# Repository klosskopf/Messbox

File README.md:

Dieses Repository beinhaltet alle Dateien zum Projekt Messbox 2000

Im Ordner *Raspberry* befindet sich der QT 5.11.3 C++ Code für die Middleware und Kennlinienerzeugung
Die Software muss mit root-Rechten ausgeführt werden. Damit die Aplikation ein Gui anzeigen kann,  
muss ```export XAUTHORITY=/home/pi/.Xauthority``` an /etc/profiles angehängt werden.

Im Ordner *Basisplatine* findet sich der Schaltplan und Layout für die Basisplatine

Im Ordner *STM32* befindet sich der C Code für die STM32 uC

Im Ordner *Steckkarte* befindet sich der Schaltplan und Layout für die Steckkarte.

Im Ordner *ATMEGA88* befindet sich der C Code für den atmega88 zur Erzeugung der sample frequenz und allgemeines

Im Ordner *BOM* finden sich Stücklisten und Bestellungsinfos für JLCPCB

Im Ordner *doc* finden sich alle Schemata, die das System beschreiben

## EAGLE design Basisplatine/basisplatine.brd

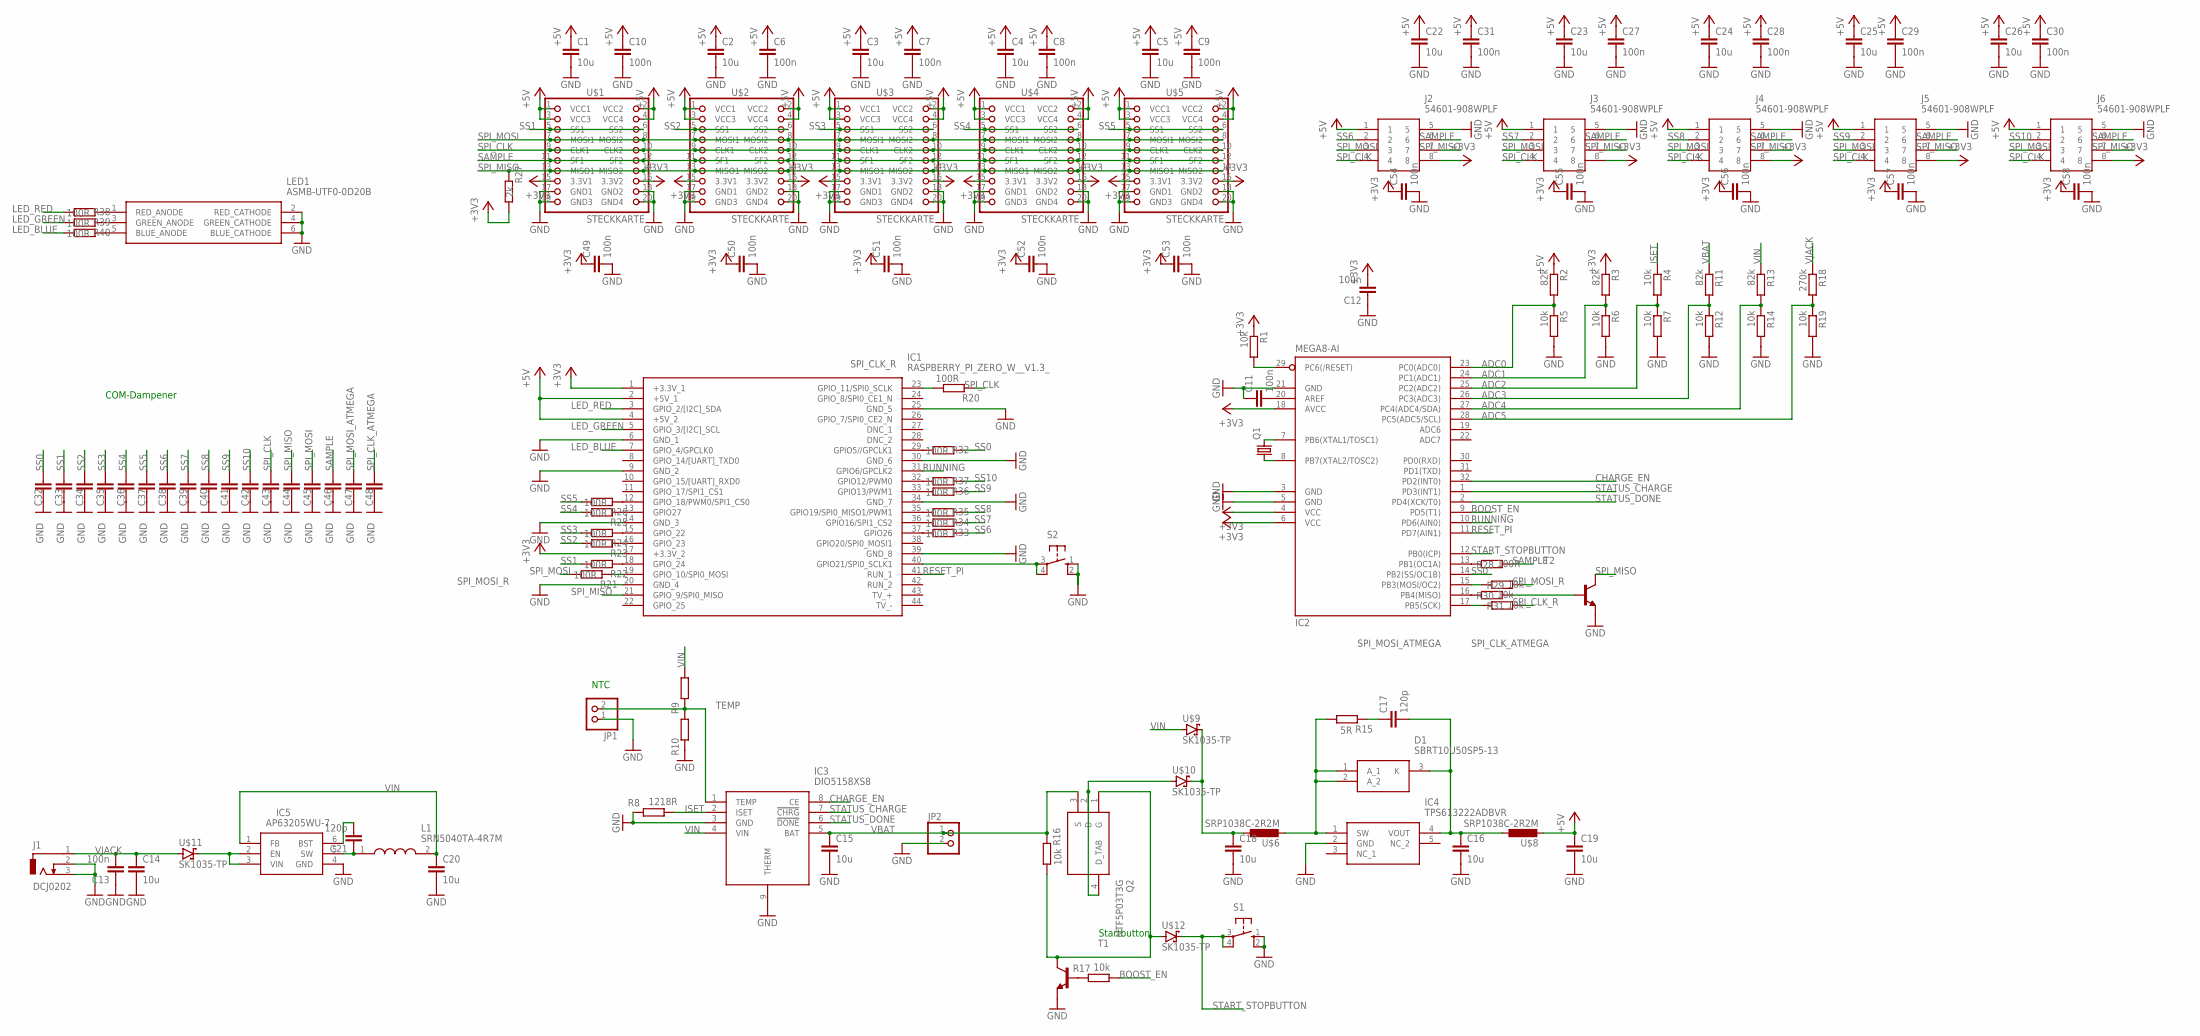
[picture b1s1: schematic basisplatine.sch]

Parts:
C1, C22: 10u; C1206
C2, C3, C4, C5, C14, C15, C16, C18, C19, C20, C23, C24, C25, C26: 10u; C1206K
C6, C7, C8, C9, C10, C11, C12, C13, C27, C28, C29, C30, C31, C49, C50, C51, C52, C53, C54, C55, C56, C57, C58: 100n; C0603K
C17, C21: 120p; C0603K
C32, C33, C34, C35, C36, C37, C38, C39, C40, C41, C42, C43, C44, C45, C46, C47, C48: C-EUC0603K; C0603K
D1: SBRT10U50SP5-13; SBRT10U50SP513
IC1: RASPBERRY_PI_ZERO_W__V1.3_; RASPBERRYPIZEROWV13
IC2: MEGA8-AI; TQFP32-08
IC3: DIO5158XS8; SOIC127P600X170-9N
IC4: TPS613222ADBVR; SOT95P280X145-5N
IC5: AP63205WU-7; SOT95P280X100-6N
J1: DCJ0202
J2, J3, J4, J5, J6: 54601-908WPLF; 54601908WPLF
JP1, JP2: PINHD-1X2; 1X02
L1: SRN5040TA-4R7M; SRN5040TA4R7M
LED1: ASMB-UTF0-0D20B; ASMBUTF00D20B
Q1: CRYSTALTC38H; TC38H
Q2: NTF5P03T3G; SOT230P700X175-4N
R1, R4, R5, R6, R7, R12, R14, R16, R17, R19, R29, R30, R31: 10k; R0603
R2, R3, R11, R13: 82k; R0603
R8: 1218R; R0603
R9, R10: R-EU_R0603; R0603
R15: 5R; R0603
R18: 270k; R0603
R20, R21, R22, R23, R24, R25, R26, R28, R32, R33, R34, R35, R36, R37, R38, R39, R40: 100R; R0603
R27: 2k; R0603
S1, S2: 10-XX; B3F-10XX
T1, T2: BC808-NPN-SOT23-BEC; SOT23-BEC
U$1, U$2, U$3, U$4, U$5: STECKKARTE; 2X10
U$6, U$8: SRP1038C-2R2M
U$9, U$10, U$11, U$12: SK1035-TP; INDC2520X120N

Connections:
+3V3: C12.2, C49.1, C50.1, C51.1, C52.1, C53.1, C54.1, C55.1, C56.1, C57.1, C58.1, IC1.1 (+3.3V_1), IC1.17 (+3.3V_2), IC2.4 (VCC), IC2.6 (VCC), IC2.18 (AVCC), J2.8, J3.8, J4.8, J5.8, J6.8, R1.1, R3.1, R27.2, U$1.15 (3.3V1), U$1.16 (3.3V2), U$2.15 (3.3V1), U$2.16 (3.3V2), U$3.15 (3.3V1), U$3.16 (3.3V2), U$4.15 (3.3V1), U$4.16 (3.3V2), U$5.15 (3.3V1), U$5.16 (3.3V2)
+5V: C1.1, C2.1, C3.1, C4.1, C5.1, C6.1, C7.1, C8.1, C9.1, C10.1, C19.1, C22.1, C23.1, C24.1, C25.1, C26.1, C27.1, C28.1, C29.1, C30.1, C31.1, IC1.2 (+5V_1), IC1.4 (+5V_2), J2.1, J3.1, J4.1, J5.1, J6.1, R2.1, U$1.1 (VCC1), U$1.2 (VCC2), U$1.3 (VCC3), U$1.4 (VCC4), U$2.1 (VCC1), U$2.2 (VCC2), U$2.3 (VCC3), U$2.4 (VCC4), U$3.1 (VCC1), U$3.2 (VCC2), U$3.3 (VCC3), U$3.4 (VCC4), U$4.1 (VCC1), U$4.2 (VCC2), U$4.3 (VCC3), U$4.4 (VCC4), U$5.1 (VCC1), U$5.2 (VCC2), U$5.3 (VCC3), U$5.4 (VCC4), U$8.P$2 (2)
ADC0: IC2.23 (PC0(ADC0)), R2.2, R5.1
ADC1: IC2.24 (PC1(ADC1)), R3.2, R6.1
ADC2: IC2.25 (PC2(ADC2)), R4.2, R7.1
ADC3: IC2.26 (PC3(ADC3)), R11.2, R12.1
ADC4: IC2.27 (PC4(ADC4/SDA)), R13.2, R14.1
ADC5: IC2.28 (PC5(ADC5/SCL)), R18.2, R19.1
BOOST_EN: IC2.9 (PD5(T1)), R17.2
CHARGE_EN: IC2.32 (PD2(INT0)), IC3.8 (CE)
CLOCK_EN: IC2.29 (PC6(/RESET)), R1.2
GND: C1.2, C2.2, C3.2, C4.2, C5.2, C6.2, C7.2, C8.2, C9.2, C10.2, C11.1, C12.1, C13.1, C14.2, C15.2, C16.2, C18.2, C19.2, C20.2, C22.2, C23.2, C24.2, C25.2, C26.2, C27.2, C28.2, C29.2, C30.2, C31.2, C32.1, C33.1, C34.1, C35.1, C36.1, C37.1, C38.1, C39.1, C40.1, C41.1, C42.1, C43.1, C44.1, C45.1, C46.1, C47.1, C48.1, C49.2, C50.2, C51.2, C52.2, C53.2, C54.2, C55.2, C56.2, C57.2, C58.2, IC1.6 (GND_1), IC1.9 (GND_2), IC1.14 (GND_3), IC1.20 (GND_4), IC1.25 (GND_5), IC1.30 (GND_6), IC1.34 (GND_7), IC1.39 (GND_8), IC2.3 (GND), IC2.5 (GND), IC2.21 (GND), IC3.3 (GND), IC3.9 (THERM), IC4.2 (GND), IC5.4 (GND), J1.2, J1.3, J2.5, J3.5, J4.5, J5.5, J6.5, JP1.1, JP2.2, LED1.2 (RED_CATHODE), LED1.4 (GREEN_CATHODE), LED1.6 (BLUE_CATHODE), R5.2, R6.2, R7.2, R8.1, R10.1, R12.2, R14.2, R19.2, S1.1 (S), S1.2 (S1), S2.1 (S), S2.2 (S1), T1.E, T2.E, U$1.17 (GND1), U$1.18 (GND2), U$1.19 (GND3), U$1.20 (GND4), U$2.17 (GND1), U$2.18 (GND2), U$2.19 (GND3), U$2.20 (GND4), U$3.17 (GND1), U$3.18 (GND2), U$3.19 (GND3), U$3.20 (GND4), U$4.17 (GND1), U$4.18 (GND2), U$4.19 (GND3), U$4.20 (GND4), U$5.17 (GND1), U$5.18 (GND2), U$5.19 (GND3), U$5.20 (GND4)
ISET: IC3.2 (ISET), R4.1, R8.2
LED_BLUE: IC1.7 (GPIO_4/GPCLK0), R40.2
LED_GREEN: IC1.5 (GPIO_3/[I2C]_SCL), R39.2
LED_RED: IC1.3 (GPIO_2/[I2C]_SDA), R38.2
unnamed: D1.1 (A_1), D1.2 (A_2), IC4.1 (SW), R15.2, U$6.P$2 (2)
unnamed: C11.2, IC2.20 (AREF)
unnamed: IC2.7 (PB6(XTAL1/TOSC1)), Q1.2
unnamed: IC2.8 (PB7(XTAL2/TOSC2)), Q1.1
unnamed: IC5.2 (EN), IC5.3 (VIN), U$11.2 (C)
unnamed: C21.1, IC5.5 (SW), L1.1
unnamed: C17.1, R15.1
unnamed: C16.1, C17.2, D1.3 (K), IC4.4 (VOUT), U$8.P$1 (1)
unnamed: C18.1, U$6.P$1 (1), U$9.2 (C), U$10.2 (C)
unnamed: R17.1, T1.B
unnamed: Q2.2 (D), Q2.4 (D_TAB), U$10.1 (A)
unnamed: C21.2, IC5.6 (BST)
unnamed: R30.2, T2.B
unnamed: IC1.18 (GPIO_24), R22.1
unnamed: IC1.16 (GPIO_23), R23.1
unnamed: IC1.15 (GPIO_22), R24.1
unnamed: IC1.13 (GPIO27), R25.1
unnamed: IC1.12 (GPIO_18/PWM0/SPI1_CS0), R26.1
unnamed: IC2.13 (PB1(OC1A)), R28.1
unnamed: IC1.40 (GPIO21/SPI0_SCLK1), S2.3, S2.4 (P1)
unnamed: IC2.16 (PB4(MISO)), R30.1
unnamed: Q2.1 (G), R16.2, T1.C, U$12.1 (A)
unnamed: IC1.29 (GPIO5//GPCLK1), R32.2
unnamed: IC1.32 (GPIO12/PWM0), R37.2
unnamed: IC1.33 (GPIO13/PWM1), R36.2
unnamed: IC1.35 (GPIO19/SPI0_MISO1/PWM1), R35.2
unnamed: IC1.36 (GPIO16/SPI1_CS2), R34.2
unnamed: IC1.37 (GPIO26), R33.2
unnamed: LED1.1 (RED_ANODE), R38.1
unnamed: LED1.3 (GREEN_ANODE), R39.1
unnamed: LED1.5 (BLUE_ANODE), R40.1
RESET_PI: IC1.41 (RUN_1), IC2.11 (PD7(AIN1))
RUNNING: IC1.31 (GPIO6/GPCLK2), IC2.10 (PD6(AIN0))
SAMPLE: C46.2, J2.6, J3.6, J4.6, J5.6, J6.6, R28.2, U$1.11 (SF1), U$1.12 (SF2), U$2.11 (SF1), U$2.12 (SF2), U$3.11 (SF1), U$3.12 (SF2), U$4.11 (SF1), U$4.12 (SF2), U$5.11 (SF1), U$5.12 (SF2)
SPI_CLK: C43.2, J2.4, J3.4, J4.4, J5.4, J6.4, R20.1, U$1.9 (CLK1), U$1.10 (CLK2), U$2.9 (CLK1), U$2.10 (CLK2), U$3.9 (CLK1), U$3.10 (CLK2), U$4.9 (CLK1), U$4.10 (CLK2), U$5.9 (CLK1), U$5.10 (CLK2)
SPI_CLK_ATMEGA: C48.2, IC2.17 (PB5(SCK)), R31.1
SPI_CLK_R: IC1.23 (GPIO_11/SPI0_SCLK), R20.2, R31.2
SPI_MISO: C44.2, IC1.21 (GPIO_9/SPI0_MISO), J2.7, J3.7, J4.7, J5.7, J6.7, R27.1, T2.C, U$1.13 (MISO1), U$1.14 (MISO2), U$2.13 (MISO1), U$2.14 (MISO2), U$3.13 (MISO1), U$3.14 (MISO2), U$4.13 (MISO1), U$4.14 (MISO2), U$5.13 (MISO1), U$5.14 (MISO2)
SPI_MOSI: C45.2, J2.3, J3.3, J4.3, J5.3, J6.3, R21.2, U$1.7 (MOSI1), U$1.8 (MOSI2), U$2.7 (MOSI1), U$2.8 (MOSI2), U$3.7 (MOSI1), U$3.8 (MOSI2), U$4.7 (MOSI1), U$4.8 (MOSI2), U$5.7 (MOSI1), U$5.8 (MOSI2)
SPI_MOSI_ATMEGA: C47.2, IC2.15 (PB3(MOSI/OC2)), R29.1
SPI_MOSI_R: IC1.19 (GPIO_10/SPI0_MOSI), R21.1, R29.2
SS0: C32.2, IC2.14 (PB2(SS/OC1B)), R32.1
SS1: C33.2, R22.2, U$1.5 (SS1), U$1.6 (SS2)
SS2: C34.2, R23.2, U$2.5 (SS1), U$2.6 (SS2)
SS3: C35.2, R24.2, U$3.5 (SS1), U$3.6 (SS2)
SS4: C36.2, R25.2, U$4.5 (SS1), U$4.6 (SS2)
SS5: C37.2, R26.2, U$5.5 (SS1), U$5.6 (SS2)
SS6: C38.2, J2.2, R33.1
SS7: C39.2, J3.2, R34.1
SS8: C40.2, J4.2, R35.1
SS9: C41.2, J5.2, R36.1
SS10: C42.2, J6.2, R37.1
START_STOPBUTTON: IC2.12 (PB0(ICP)), S1.3, S1.4 (P1), U$12.2 (C)
STATUS_CHARGE: IC2.1 (PD3(INT1)), IC3.7 (!CHRG)
STATUS_DONE: IC2.2 (PD4(XCK/T0)), IC3.6 (!DONE)
TEMP: IC3.1 (TEMP), JP1.2, R9.1, R10.2
VBAT: C15.1, IC3.5 (BAT), JP2.1, Q2.3 (S), R11.1, R16.1
VIN: C20.1, IC3.4 (VIN), IC5.1 (FB), L1.2, R9.2, R13.1, U$9.1 (A)
VJACK: C13.2, C14.1, J1.1, R18.1, U$11.1 (A)

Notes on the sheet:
NTC
Startbutton
COM-Dampener

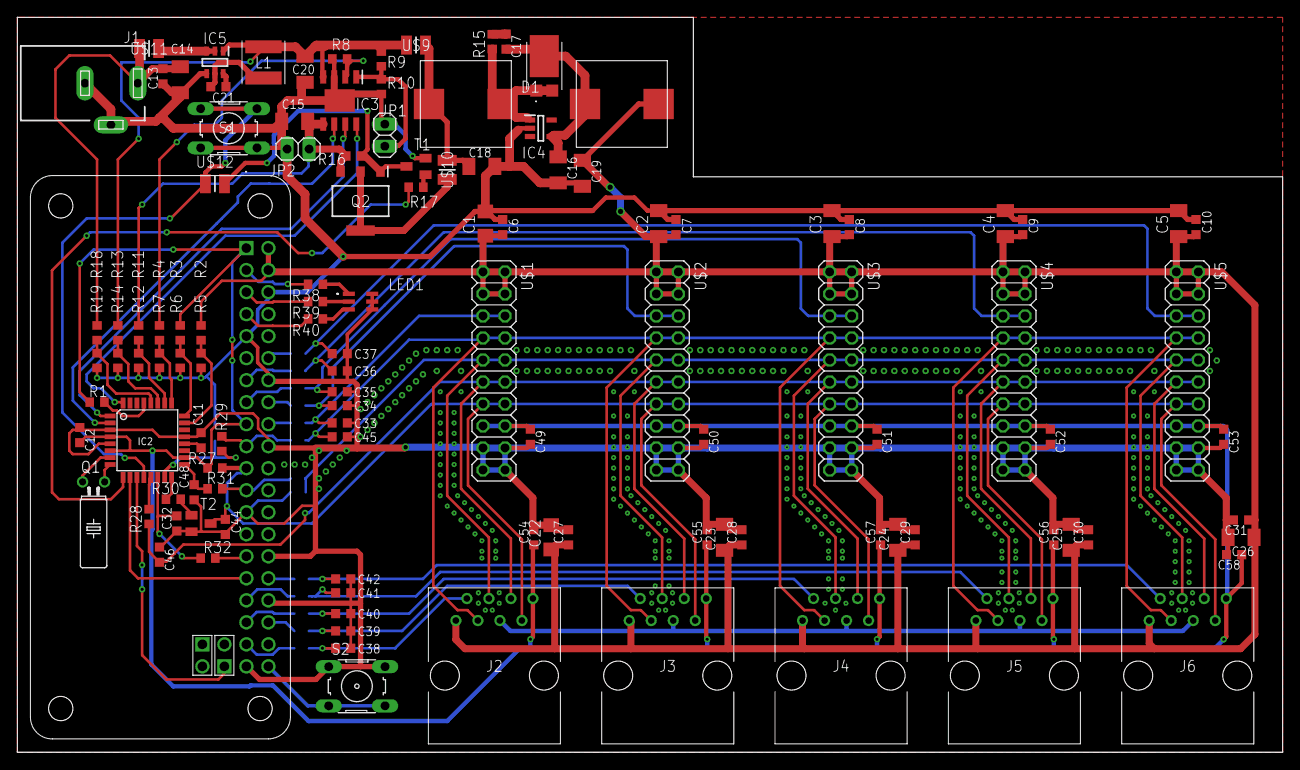
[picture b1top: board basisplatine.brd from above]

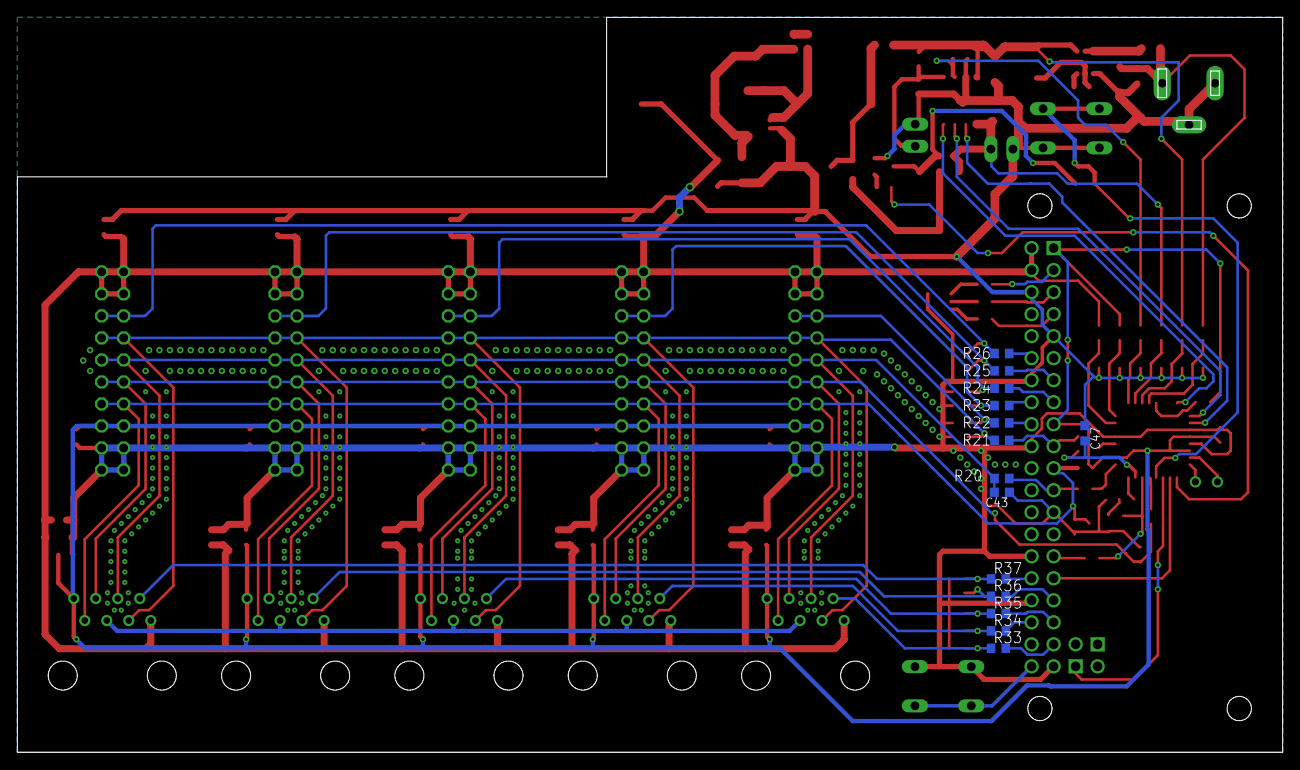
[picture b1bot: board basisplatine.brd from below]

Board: 2 copper layers, 146.0 x 84.8 mm, 131 parts (14 on the bottom side), 75 nets.

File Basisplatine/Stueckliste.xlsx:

Bauteil | Bezeichnung | Bauteil | Bestellnummer | Shop | Menge | Preis einzel | Preis
U1,U2,U3,U4,U5 | 20pin Stecker | BLG2X10 | 1492267 - 62 | Conrad | 5 | 0.32 | 1.6
IC1 | RaspberryPi 0 w | Raspberry Pi® Zero W | 3272496006997 | Mercateo | 1 | 21.34 | 21.34
IC3 | Laderegler | DIO5158XS8 | 453-DIO5158XS8 | Mouser | 1 | 0.57999999999999996 | 0.57999999999999996
IC4 | Boost-Converter | TPS613222ADBVR | 595-TPS613222ADBVR | Mouser | 1 | 0.92 | 0.92
IC5 | Buck-Converter | AP63205WU-7 | 621-AP63205WU-7 | Mouser | 1 | 1.31 | 1.31
Q1 | 32kHz Quarz | LFXTAL002996Bulk | 449-LFXTAL002996BULK | Mouser | 1 | 0.26 | 0.26
Q2 | discharge-Transistor | NTF5P03T3G | 863-NTF5P03T3G | Mouser | 1 | 0.28000000000000003 | 0.28000000000000003
T1,T2 | hold-on-transistor | BCW66HVL | 771-BCW66HVL | Mouser | 2 | 0.17 | 0.34
L1 | Buck-Spule | SRN5040TA-4R7M | 652-SRN5040TA-4R7M | Mouser | 1 | 0.34 | 0.34
U6,U8 | Boost-Spule | SRP1038C-2R2M | 652-SRP1038C-2R2M | Mouser | 2 | 1.06 | 2.12
U7 | Schottky-Diode | SBRT10U50SP5-13 | 621-SBRT10U50SP5-13 | Mouser | 1 | 0.61 | 0.61
U9,U10,U11,U12 | Schottky-Diode | SK33-TP | 833-SK33-TP | Mouser | 4 | 0.35 | 1.4
R15 | 5R 0603 | CRCW06034R99FKEA | 71-CRCW0603-4.99-E3 | Mouser | 1 | 0.1 | 0.1
R28,R26,R25,R24,R23,R22,R21,R20,R32,R37,R36,R35,R34,R33,R38,R39,R40 | 100R 0603 | CRCW0603100RFKEAC | 71-CRCW0603100RFKEAC | Mouser | 17 | 2.3E-2 | 0.39100000000000001
R8 | 1k2 0603 | ERJ-3RBD1201V | 667-ERJ-3RBD1201V | Mouser | 1 | 0.1 | 0.1
R27 | 2k 0603 | RR0816P-202-D | 754-RR0816P-202D | Mouser | 1 | 0.1 | 0.1
R1,R16,R17,R29,R30,R31,R5,R6,R7,R12,R14,R19, R4 | 10k 0603 | RR0816P-103-D | 754-RR0816P-103D | Mouser | 13 | 8.1000000000000003E-2 | 1.0529999999999999
R2,R3,R11,R13 | 82k 0603 | RR0816P-823-D | 754-RR0816P-823D | Mouser | 4 | 0.1 | 0.4
R18 | 270k 0603 | RR0816P-274-D | 754-RR0816P-274D | Mouser | 1 | 0.1 | 0.1
J1 | DC-Jack | KLDX-0202-AC | 806-KLDX-0202-AC | Mouser | 1 | 0.44 | 0.44
J2,J3,J4,J5,J6 | RJ45-Buchse | 54601-908WPLF | 649-54601-908WPLF | Mouser | 5 | 0.54 | 2.7
C17,C21 | 120pF 0603 | C0603C121J5GAC | 80-C0603C121J5GAC | Mouser | 2 | 0.1 | 0.2
C11,C13,C12,C10,C6,C7,C8,C9,C31,C27,C28,C29,C30,C49,C50,C51,C52,C53,C54,C55,C56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 | 100nF 0603 | 0603B104J500CT | 791-0603B104J500CT | Mouser | 23 | 0.108 | 2.484
C14,C15,C16,C19,C20,C18,C1,C2,C3,C4,C5,C22,C23,C24,C25,C26 | 10uF 1206 | 1206DD106MAT2A | 581-1206DD106MAT2A | Mouser | 16 | 0.20899999999999999 | 3.3439999999999999
LED1 | RGB-LED | PLCC-6 |  | selbst | 1 | 0 | 0
S1 | Taster | DIP-TASTER |  | selbst | 2 | 0 | 0
JP1 | NTC | NTC |  | selbst | 1 | 0 | 0
IC2 | Atmega88 | ATMEGA88PB-AU |  | selbst | 1 | 0 | 0
 |  |  |  |  |  |  | 42.512000000000008

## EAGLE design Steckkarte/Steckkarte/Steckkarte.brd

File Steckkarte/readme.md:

Mein Vorschlag als IDE:
Eclipse mit STM32 plugin:

1. Stlink-Treiber: https://my.st.com/content/my_st_com/en/products/development-tools/software-development-tools/stm32-software-development-tools/stm32-utilities/stsw-link009.html  
2. Stlink-Utility: https://my.st.com/content/my_st_com/en/products/development-tools/software-development-tools/stm32-software-development-tools/stm32-programmers/stsw-link004.html  
3. CubeMX: https://my.st.com/content/my_st_com/en/products/development-tools/software-development-tools/stm32-software-development-tools/stm32-configurators-and-code-generators/stm32cubemx.html#tools-software  
4. Java: https://java.com/de/download/  
5. Eclipse: https://www.eclipse.org/downloads/  
In Eclipse: help -> Install new software -> work with:  
6. STM32 plugin: http://ac6-tools.com/Eclipse-updates/org.openstm32.system-workbench.update-site-v2

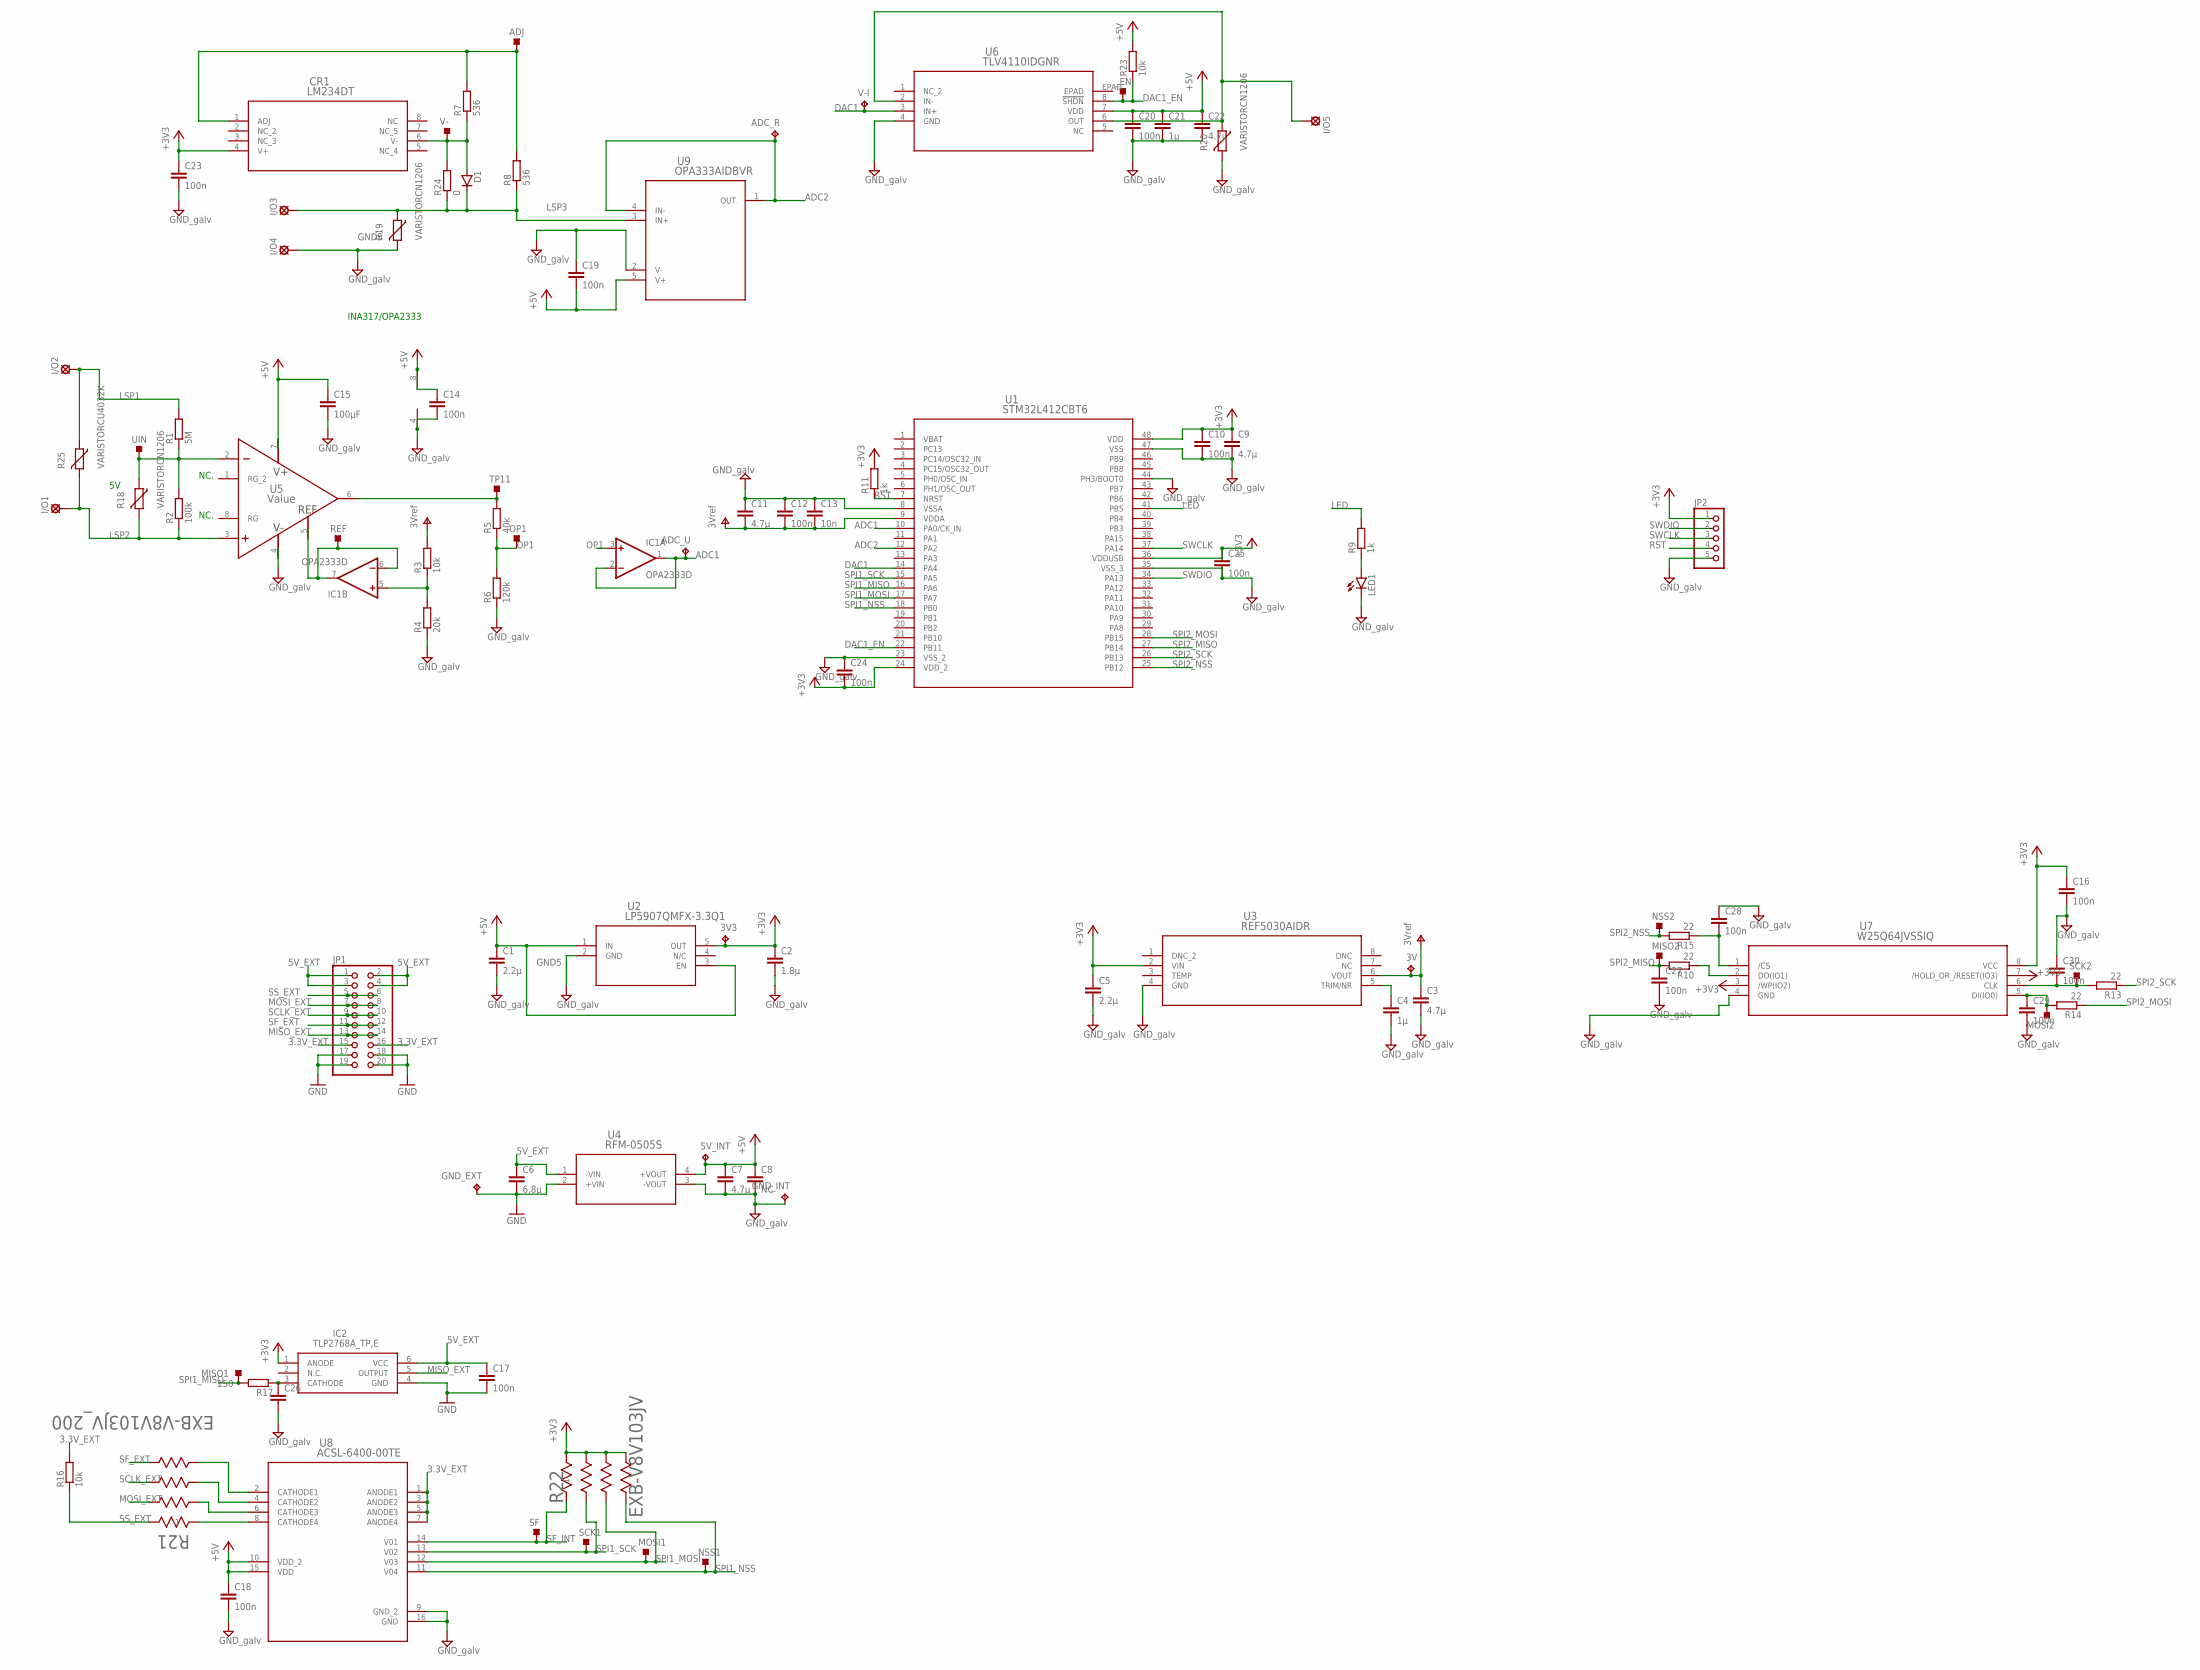
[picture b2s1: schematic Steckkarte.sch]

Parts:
3V, 3V3, 5V_INT: TPPAD1-13; P1-13
ADC_R: TPPAD1-13; P1-13
ADC_U: TPPAD1-13; P1-13
ADJ: TESTPOINT_TPS-SMD-10SN; TESTPOINT_SMD-10SN
C1, C5: 2.2µ; C0603K
C2: 1.8µ; C1206K
C3, C7, C9, C11, C22: 4.7µ; C0603K
C4, C21: 1µ; C0603K
C6: 6,8µ; C0603K
C8: NC; C0603K
C10, C12, C14, C16, C17, C18, C19, C20, C23, C24, C25, C27, C28, C29, C30: 100n; C0603K
C13: 10n; C0603K
C15: 100µF; C1206K
C26: C-EUC0603K; C0603K
CR1: LM234DT; SO-8
D1: D-SOD123; SOD123
GND_EXT: TPPAD1-13; P1-13
GND_INT: TPPAD1-13; P1-13
I/O1, I/O2, I/O3, I/O4, I/O5: SE14
IC1: OPA2333D; SO08
IC2: TLP2768A_TP,E; SOIC127P1000X220-6N
JP1: PINHD-2X10/90; 2X10/90
JP2: PINHD-1X5; 1X05
LED1: LED5MM
MISO1, MISO2: TESTPOINT_TPS-SMD-10SN; TESTPOINT_SMD-10SN
MOSI1, MOSI2: TESTPOINT_TPS-SMD-10SN; TESTPOINT_SMD-10SN
NSS1, NSS2: TESTPOINT_TPS-SMD-10SN; TESTPOINT_SMD-10SN
OP1: TESTPOINT_TPS-SMD-10SN; TESTPOINT_SMD-10SN
R1: 5M; R1206
R2: 100k; R1206
R3, R16, R23: 10k; R0603
R4: 20k; R0603
R5: 40k; R0603
R6: 120k; R0603
R7, R8: 536; R0603
R9, R11: 1k; R0603
R10, R13, R14, R15: 22; R0603
R17: 150; R0603
R18, R19, R20: VARISTORCN1206; CT/CN1206
R21: EXB-V8V103JV_200; EXBV8V
R22: EXB-V8V103JV; EXBV8V
R24: 0; R0603
R25: VARISTORCU4032K; CU4032K
REF: TESTPOINT_TPS-SMD-10SN; TESTPOINT_SMD-10SN
SCK1, SCK2: TESTPOINT_TPS-SMD-10SN; TESTPOINT_SMD-10SN
SF: TESTPOINT_TPS-SMD-10SN; TESTPOINT_SMD-10SN
TP11: TESTPOINT_TPS-SMD-10SN; TESTPOINT_SMD-10SN
U1: STM32L412CBT6; LQFP-48
U2: LP5907QMFX-3.3Q1; DBV5
U3: REF5030AIDR; D8
U4: RFM-0505S
U5: Value; DGK0008A_N
U6: TLV4110IDGNR; DGN8_1P89X1P57
U7: W25Q64JVSSIQ; SOIC-8_5P28X5P28
U8: ACSL-6400-00TE; SOIC_6400-00TE
U9: OPA333AIDBVR; DBV5
UIN: TESTPOINT_TPS-SMD-10SN; TESTPOINT_SMD-10SN
V-: TESTPOINT_TPS-SMD-10SN; TESTPOINT_SMD-10SN
V-I: TPPAD1-13; P1-13
_EN: TESTPOINT_TPS-SMD-10SN; TESTPOINT_SMD-10SN

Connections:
3.3V_EXT: JP1.15, JP1.16, R16.2, U8.1 (ANODE1), U8.3 (ANODE2), U8.5 (ANODE3), U8.7 (ANODE4)
5V_EXT: C6.1, C17.1, IC2.6 (VCC), JP1.1, JP1.2, JP1.3, JP1.4, U4.1 (-VIN)
+3V3: 3V3.TP, C2.1, C5.1, C9.1, C10.1, C16.1, C23.1, C24.2, C25.1, CR1.4 (V+), IC2.1 (ANODE), JP2.1, R11.2, R22.5, R22.6, R22.7, R22.8, U1.24 (VDD_2), U1.36 (VDDUSB), U1.48 (VDD), U2.5 (OUT), U3.2 (VIN), U7.3 (/WP(IO2)), U7.7 (/HOLD_OR_/RESET(IO3)), U7.8 (VCC)
+5V: 5V_INT.TP, C1.1, C7.1, C8.1, C14.1, C15.1, C18.1, C19.2, C20.1, C21.1, C22.1, IC1.8 (V+), R23.2, U2.1 (IN), U2.3 (EN), U4.4 (+VOUT), U5.7 (V+), U6.7 (VDD), U8.10 (VDD_2), U8.15 (VDD), U9.5 (V+)
ADC1: ADC_U.TP, IC1.1 (OUT), IC1.2 (-IN), U1.10 (PA0/CK_IN)
ADC2: ADC_R.TP, U1.12 (PA2), U9.1 (OUT), U9.4 (IN-)
DAC1: U1.14 (PA4), U6.3 (IN+), V-I.TP
DAC1_EN: R23.1, U1.22 (PB11), U6.8 (!SHDN), _EN.TP
GND: C6.2, C17.2, GND_EXT.TP, IC2.4 (GND), JP1.17, JP1.18, JP1.19, JP1.20, U4.2 (+VIN)
GND5: C1.2, C2.2, C3.2, C4.2, C5.2, C7.2, C8.2, C9.2, C10.2, C11.1, C12.1, C13.1, C14.2, C15.2, C16.2, C18.2, C19.1, C20.2, C21.2, C22.2, C23.2, C24.1, C25.2, C26.2, C27.2, C28.1, C29.2, C30.1, GND_INT.TP, I/O4.MP, IC1.4 (V-), JP2.5, LED1.K (C), R4.1, R6.1, R19.2, R20.2, U1.8 (VSSA), U1.23 (VSS_2), U1.35 (VSS_3), U1.44 (PH3/BOOT0), U1.47 (VSS), U2.2 (GND), U3.4 (GND), U4.3 (-VOUT), U5.4 (V-), U6.4 (GND), U7.4 (GND), U8.9 (GND_2), U8.16 (GND), U9.2 (V-)
LED: R9.2, U1.41 (PB5)
LSP1: I/O2.MP, R1.2, R25.1
LSP2: I/O1.MP, R2.1, R18.2, R25.2, U5.3 (IN+)
LSP3: D1.1 (C), I/O3.MP, R8.1, R19.1, R24.1, U9.3 (IN+)
LSP5: I/O5.MP, R20.1, U6.2 (IN-), U6.6 (OUT)
MISO_EXT: IC2.5 (OUTPUT), JP1.13, JP1.14
MOSI_EXT: JP1.7, JP1.8, R21.7
unnamed: LED1.A, R9.1
unnamed: R1.1, R2.2, R18.1, U5.2 (IN-), UIN.TP
unnamed: R10.1, U7.2 (DO(IO1))
unnamed: R5.2, TP11.TP, U5.6 (OUT)
unnamed: IC1.5 (+IN), R3.1, R4.2
unnamed: C4.1, U3.5 (TRIM/NR)
unnamed: IC1.6 (-IN), IC1.7 (OUT), REF.TP, U5.5 (REF)
unnamed: R21.1, U8.8 (CATHODE4)
unnamed: CR1.6 (V-), D1.2 (A), R7.1, R24.2, V-.TP
unnamed: ADJ.TP, CR1.1 (ADJ), R7.2, R8.2
unnamed: C30.2, R13.2, SCK2.TP, U7.6 (CLK)
unnamed: C29.1, MOSI2.TP, R14.2, U7.5 (DI(IO0))
unnamed: C28.2, R15.1, U7.1 (/CS)
unnamed: R21.2, U8.6 (CATHODE3)
unnamed: R21.3, U8.4 (CATHODE2)
unnamed: R21.4, U8.2 (CATHODE1)
unnamed: C26.1, IC2.3 (CATHODE), R17.1
OP1: IC1.3 (+IN), OP1.TP, R5.1, R6.2
RST: JP2.4, R11.1, U1.7 (NRST)
SCLK_EXT: JP1.9, JP1.10, R21.6
SF_EXT: JP1.11, JP1.12, R21.5
SF_INT: R22.1, SF.TP, U8.14 (V01)
SPI1_MISO: MISO1.TP, R17.2, U1.16 (PA6)
SPI1_MOSI: MOSI1.TP, R22.3, U1.17 (PA7), U8.12 (V03)
SPI1_NSS: NSS1.TP, R22.4, U1.18 (PB0), U8.11 (V04)
SPI1_SCK: R22.2, SCK1.TP, U1.15 (PA5), U8.13 (V02)
SPI2_MISO: C27.1, MISO2.TP, R10.2, U1.27 (PB14)
SPI2_MOSI: R14.1, U1.28 (PB15)
SPI2_NSS: NSS2.TP, R15.2, U1.25 (PB12)
SPI2_SCK: R13.1, U1.26 (PB13)
SS_EXT: JP1.5, JP1.6, R16.1, R21.8
SWCLK: JP2.3, U1.37 (PA14)
SWDIO: JP2.2, U1.34 (PA13)
V+: 3V.TP, C3.1, C11.2, C12.2, C13.2, R3.2, U1.9 (VDDA), U3.6 (VOUT)
VBAT: U1.1 (VBAT)

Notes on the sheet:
NC.
INA317/OPA2333

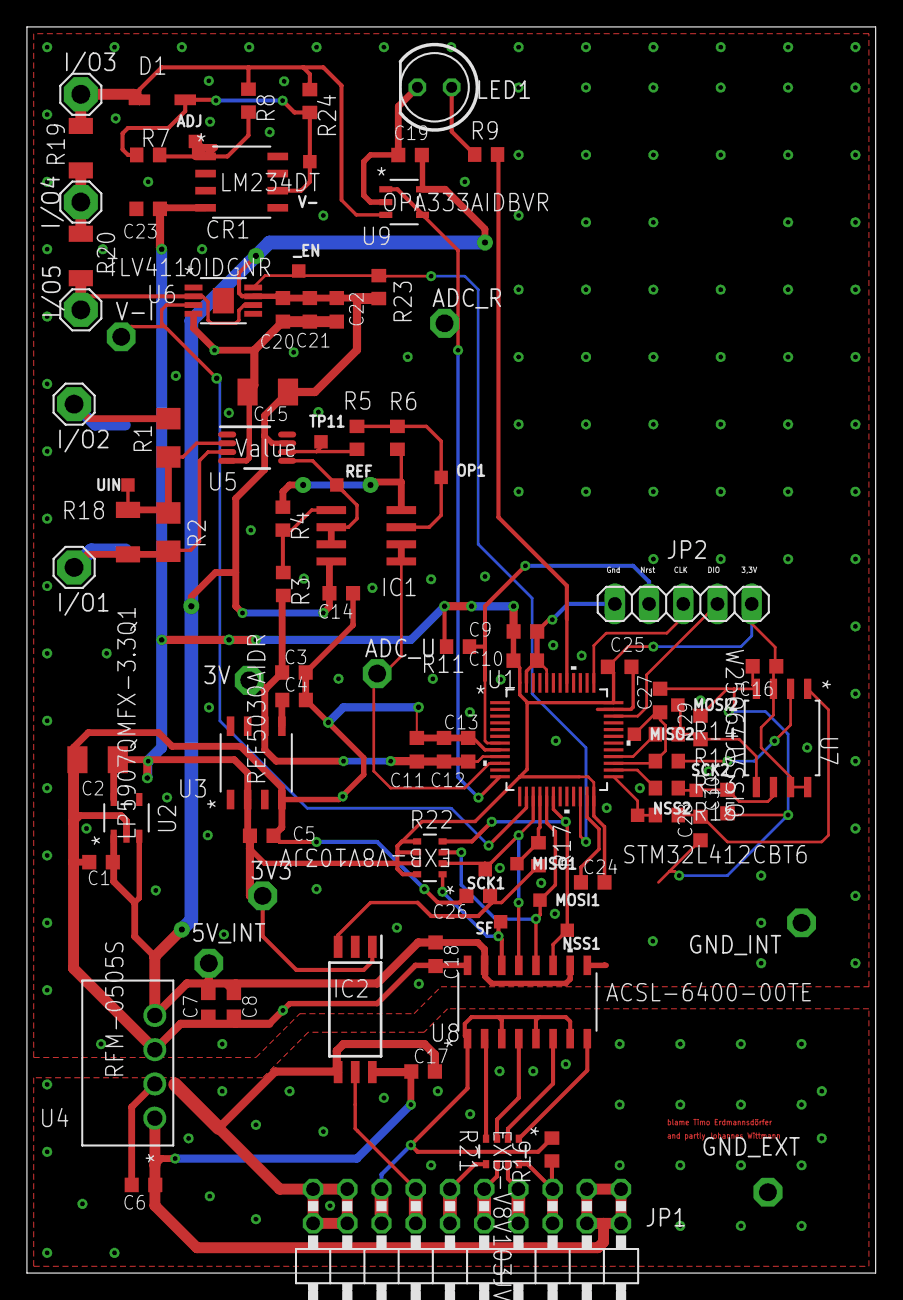
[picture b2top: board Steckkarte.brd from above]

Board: 2 copper layers, 63.0 x 92.5 mm, 99 parts (1 on the bottom side), 51 nets.

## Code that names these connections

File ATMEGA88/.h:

#ifndef global
#define global

#define CHARGE_EN PD2
#define STATUS_CHARGE PD3
#define STATUS_DONE PD4
#define BOOST_EN PD5
#define RUNNING PD6
#define RESET_PI PD7

#define START_STOPBUTTON PB0

#define SET_PRE_0 (TCCR1B=0b00011000)
#define SET_PRE_1 (TCCR1B=0b00011000)
#define SET_PRE_8 (TCCR1B=0b00011000)
#define SET_PRE_64 (TCCR1B=0b00011000)
#define SET_PRE_256 (TCCR1B=0b00011000)
#define SET_PRE_1024 (TCCR1B=0b00011000)

float samplefreq;

#endif

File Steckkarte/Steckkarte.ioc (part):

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Mcu.Name=STM32L431C(B-C)Tx
Mcu.Package=LQFP48
Mcu.UserName=STM32L431CBTx
PA0.Signal=ADCx_IN5
PA1.Mode=Full_Duplex_Slave
PA1.Signal=SPI1_SCK
PA10.Mode=Asynchronous
PA10.Signal=USART1_RX
PA11.Mode=Full_Duplex_Slave
PA11.Signal=SPI1_MISO
PA12.Mode=Full_Duplex_Slave
PA12.Signal=SPI1_MOSI
PA4.Mode=NSS_Signal_Hard_Input
PA4.Signal=SPI1_NSS
PA9.Mode=Asynchronous
PA9.Signal=USART1_TX
PB10.Mode=Full_Duplex_Master
PB10.Signal=SPI2_SCK
PB12.Mode=NSS_Signal_Hard_Output
PB12.Signal=SPI2_NSS
PB14.Mode=Full_Duplex_Master
PB14.Signal=SPI2_MISO
PB15.Mode=Full_Duplex_Master
PB15.Signal=SPI2_MOSI
PB9.Signal=GPIO_Output
RCC.HSE_VALUE=8000000
RCC.SYSCLKFreq_VALUE=16000000
RCC.SYSCLKSource=RCC_SYSCLKSOURCE_HSI
board=custom

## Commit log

2020-02-03 Added doc-Folder and schematics
2020-02-03 Added schematic pdfs
2020-02-04 Added 3d-model (or modell)
2020-02-04 Notizen
2020-02-04 Added Folders for subprojects
2020-02-04 umbenannt
2020-02-04 Added renders
2020-02-05 Modified description document
2020-02-06 Steckbrief
2020-02-06 Setup Steckkarten project and added Raspberry UML
2020-02-06 reversed actions
2020-02-07 minor change to C
2020-02-07 added GUI concept
2020-02-07 reworked SPI commands
2020-02-11 startet Raspberry Pi GUI
2020-02-14 Fixed Parameterlist
2020-02-14 Added a few gui elements
2020-02-17 Added Parameters
2020-02-18 Minor changes
2020-02-19 liste bauelemente
2020-02-29 transvere
2020-02-29 Added Control thread and Karte Destructor
2020-03-01 Added Briefkasten and Karten check routine
2020-03-05 Basisplatine: Raspberry Pi, Samplefrequenz, Steckkarten
2020-03-14 added battery managment
2020-03-15 Added dampening Cs on SPI and RJ45
2020-03-17 Startetd steckkarten-project; added driver for gpio and spi
2020-03-18 Added SPI-decoder
2020-03-20 gerber+bestelliste
2020-03-20 Added Stueckliste, Taster, LED
2020-03-20 eagel layout
2020-03-20 update layout
2020-03-20 Fixed some stuff
2020-03-21 Added 3,3V and vias to Basisplatine, ...
2020-03-24 Added parameter-decoder to raspberry
2020-03-24 Added rest of protokoll in post
2020-03-24 steckkarte die 2.te
2020-03-25 Refactored fake SPI, add get_daten, get_status, draw graph in qt thread
2020-03-25 Fixed some fucking bugs; Added graph-visualcation of data comming from SPI
2020-03-27 Added cam for Basisplatine / Bestelldaten
2020-03-31 Changed to little endian-com; Enhanced timescale at higher numbers by changing to double in chart, Added get_status
2020-04-07 Started Kennlinienerstellung
2020-04-08 Refactored graph
2020-04-09 Added next part of Kennlinienerstellung
2020-05-06 dead end of BORIS-style
2020-05-06 QT is a f****** moron
2020-05-06 Changed the GUI to text based input
2020-05-09 Added the Rechentreebuilding for Rechenfeld
2020-05-11 Added x and y Axis input decoder
2020-05-13 Started software for atmega88 (sample freq)
2020-05-26 No idea, what I did here
2020-06-26 Made stable, addes axis
2020-07-12 Added SPI interface and most of the protocol
2020-07-13 Updated spi protocoll; added dummy module
2020-07-16 Added DMA for data transferer, changed spi protokol
2020-07-16 Added start/stop, minor fixes, fuck this shit
2020-07-17 fixed some things
2020-07-17 minor fixes
2020-07-18 Added synchronized Sample Frequency and fixed priority in Steckkarte_moc
2020-07-18 Fixed some minor control problems
2020-08-03 minor fixes / savepoint
2020-08-05 Hey its fluid now / fixed negative constants
2020-08-08 Added ADC to steckkarte_moc (Sry, I had to defeat my nemesis)
2020-08-09 converted Steckkarte_moc to STM32L431CBTx
2020-08-09 Major performance boost
2020-08-14 Startet Flash_HAL
2020-08-15 Added FLASH-HAL Im tired of this shit
2020-08-17 unfinished try
2020-08-17 fixed merge
2020-08-18 Started paging
2020-08-18 enhanced post
2020-08-18 Added min/max
2020-08-19 Fixed read/write flash conflicts
2020-08-20 Hier funktioniert noch alles
2020-08-21 organized int. priority; fixed starttumeerror
2020-08-21 Added double buffering and detached buffer from parameter to save RAM
2020-08-21 FIxed the same stuff the fith time :/
2020-08-21 changed the get_parameter database to dynamic string creation
2020-08-21 fixed min/max, fixed first point=0 issuue, changed startstop axis
2020-08-22 Added save feature
2020-08-25 Added multiple ADC channels; smal adc input filter
2020-08-25 Adjusted for new card with isolation
2020-08-25 Added button start/stop
2020-08-26 restructured parameter get and set; Added triangle generator
2020-08-27 Implemented new paging. paging happens now not at EOC, but at EOS and distributed
2020-08-29 Added a short software doc
2020-08-29 "prepared a bad merge"
2020-08-29 git merge is broken af
2020-08-29 Restructured drictory structure
2020-08-30 started UML doc
2020-08-31 added simple UML for various parts of Raspberry
2020-08-31 Added short explanation of BasisplatineHardware
2020-08-31 Now with persistent parameter values
2020-09-11 Added base status aquisition and Undervoltage shutdown
2020-09-12 Added base status in gui
2020-09-12 switched from wiringpi to bcm2835 library
2020-09-15 fixed Save procedure
2020-12-08 Create LICENSE

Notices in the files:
parts and their libraries:
stm32l412CB6T: COPYRIGHT: Copyright (C) 2018 Accelerated Designs. All rights reserved
